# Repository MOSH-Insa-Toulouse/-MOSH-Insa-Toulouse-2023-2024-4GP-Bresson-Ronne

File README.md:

# -MOSH-Insa-Toulouse-2023-2024-4GP-Bresson-Ronne

Projet 4GP du capteur au banc de test en open source hardware
---
## Sommaire
  - [1) Contexte](#1-contexte)
  - [2) L'électronique Analogique](#2-L'électroniqueAnalogique)
  - [3) Kicad](#3-kicad)
  - [4) Le code Arduino](#4-lecodeArduino)
  - [5) L'application Bluetooth ](#5-l'appli)
  - [6) La DataSheet ](#6-data)
---

## 1) Contexte
Dans le cadre de l'UE "Du capteur au banc de test en Open Source Hardware", nous avons été amenés à réaliser un capteur de déformation low-tech à base de graphite. Le fonctionnement de ce capteur repose sur la variation de résistance engendrée par la déformation du matériau. La physique sous-jacente à cette variation de résistance provient du déplacement des électrons par effet tunnel entre les nanoparticules de graphite. Lorsqu'une contrainte mécanique est appliquée, la distance entre les nanoparticules varie, ce qui modifie la conductivité du graphite. Cette modification entraîne ainsi une variation de la résistance du capteur.<br>
Ce capteur est ensuite connnecté à un arduino. Divers élements sont ajoutés à l'Arduino, un capeteur flex sensor industriel que l'on comparera à notre capteur LowTech maison, un écran Oled pour pouvoir afficher nos résultats et un encodeur rotatoire qui permet de se déplacer sur les menus de l'écran Oled. Un module bluetooth est aussi implémenté en vue de créer une application android pour visualiser nos données. 

<p align="center">
  
  <br>
  <i>Photo de l'installation</i>
</p>

## 2) L'électronique Analogique
Une partie importante de la chaîne d’acquisition pour notre capteur réside dans le
conditionnement du signal délivré par le capteur, c’est-à-dire l’amplifier et le filtrer
pour pouvoir l’exploiter. Afin d’utiliser les capacités de la carte Arduino au maximum
(en pleine échelle), le gain du circuit d’amplification est variable grâce à la résistance
R2, ajustée par un potentiomètre digital.<br>
Le filtrage est effectué à plusieurs niveaux (avant et après amplification). Il y a donc 3
étages, chacun avec une fréquence de coupure différente, pour limiter le bruit au
maximum. Le circuit est modélisé dans LTSpice, afin d’effectuer des simulations. Il
faut noter qu’ici on peut se permettre d’avoir un filtrage fort à des fréquences très
faibles car à priori notre capteur ne sera pas utilisé à plus qu’environ 1Hz. Les
résultats obtenus par les simulations et un exemple de simulation (Diagramme de
Bode pour un étage sont présentés sur les figures suivantes. Le circuit LTSpice est à
trouver dans le dossier « électronique analogique ».

<p align="center">
  
  <br>
  <i>Caractéristiques de l'AOP</i>
</p>

<p align="center">
  
  <br>
  <i>Diagramme de Bode du premier étage de l'AOP</i>
</p>

## 3) Kicad
Afin de réaliser en pratique le circuit modélisé dans LTSpice, ainsi qu’ajouter tous les
composants liés à notre chaîne d’acquisition et aux capteurs, le logiciel KiCad est
utilisé. Il permet à partir d’un schéma électrique, créé dans un premier temps, et de
l’ajout des empreintes et modèles 3D des différents composants, de modéliser le
PCB et ses pistes électroniques, et d’en obtenir un modèle 3D. Ces documents sont
disponibles dans le dossier « KiCad ». Avec l’aide de Catherine Crouzet, nous avons
ensuite pu fabriquer notre PCB y souder les composants pour tester toute notre
chaîne d’acquisition, qui s’est avérée fonctionnelle directement.

<p align="center">
  
  <br>
  <i>Schéma du PCB réalisé sur KiCad</i>
</p>

## 4) Le code Arduino

Un code Arduino est implémenté sur un ArduinoUno. Le code permet d'afficher les valeurs de résistance sur l'écran oled et de choisir quel capteur est affiché via un encodeur rotatoire. Les valeurs de résitances sont aussi disponibles sur le serialmonitor ainsi que sur le téléphone. 

## 5) Lapplication 
L’application Android, créée avec le MIT App Inventor, permet de dialoguer via Bluetooth
(bouton de connexion à activer) avec la carte Arduino pour obtenir les valeurs de
résistance/angle fournies par le capteur. L’utilisateur peut choisir un nombre de mesures à
effectuer, le moment pour les lancer, puis ces mesures sont affichées en live sur un
indicateur numérique, un graphique, et exportées dans un tableur afin de les exploiter au
mieux. Un fichier APK est téléchargeable dans le dossier « Application Android »

<p align="center">
  
  <br>
  <i>Schéma de l'application Android</i>
</p>

## 6) La DataSheet 
La data sheet du capteur est disponible  [ici](https://github.com/MOSH-Insa-Toulouse/2023-2024-4GP-Bresson-Ronne/blob/main/DataSheet/datasheetCapteurBressonRonne.pdf).

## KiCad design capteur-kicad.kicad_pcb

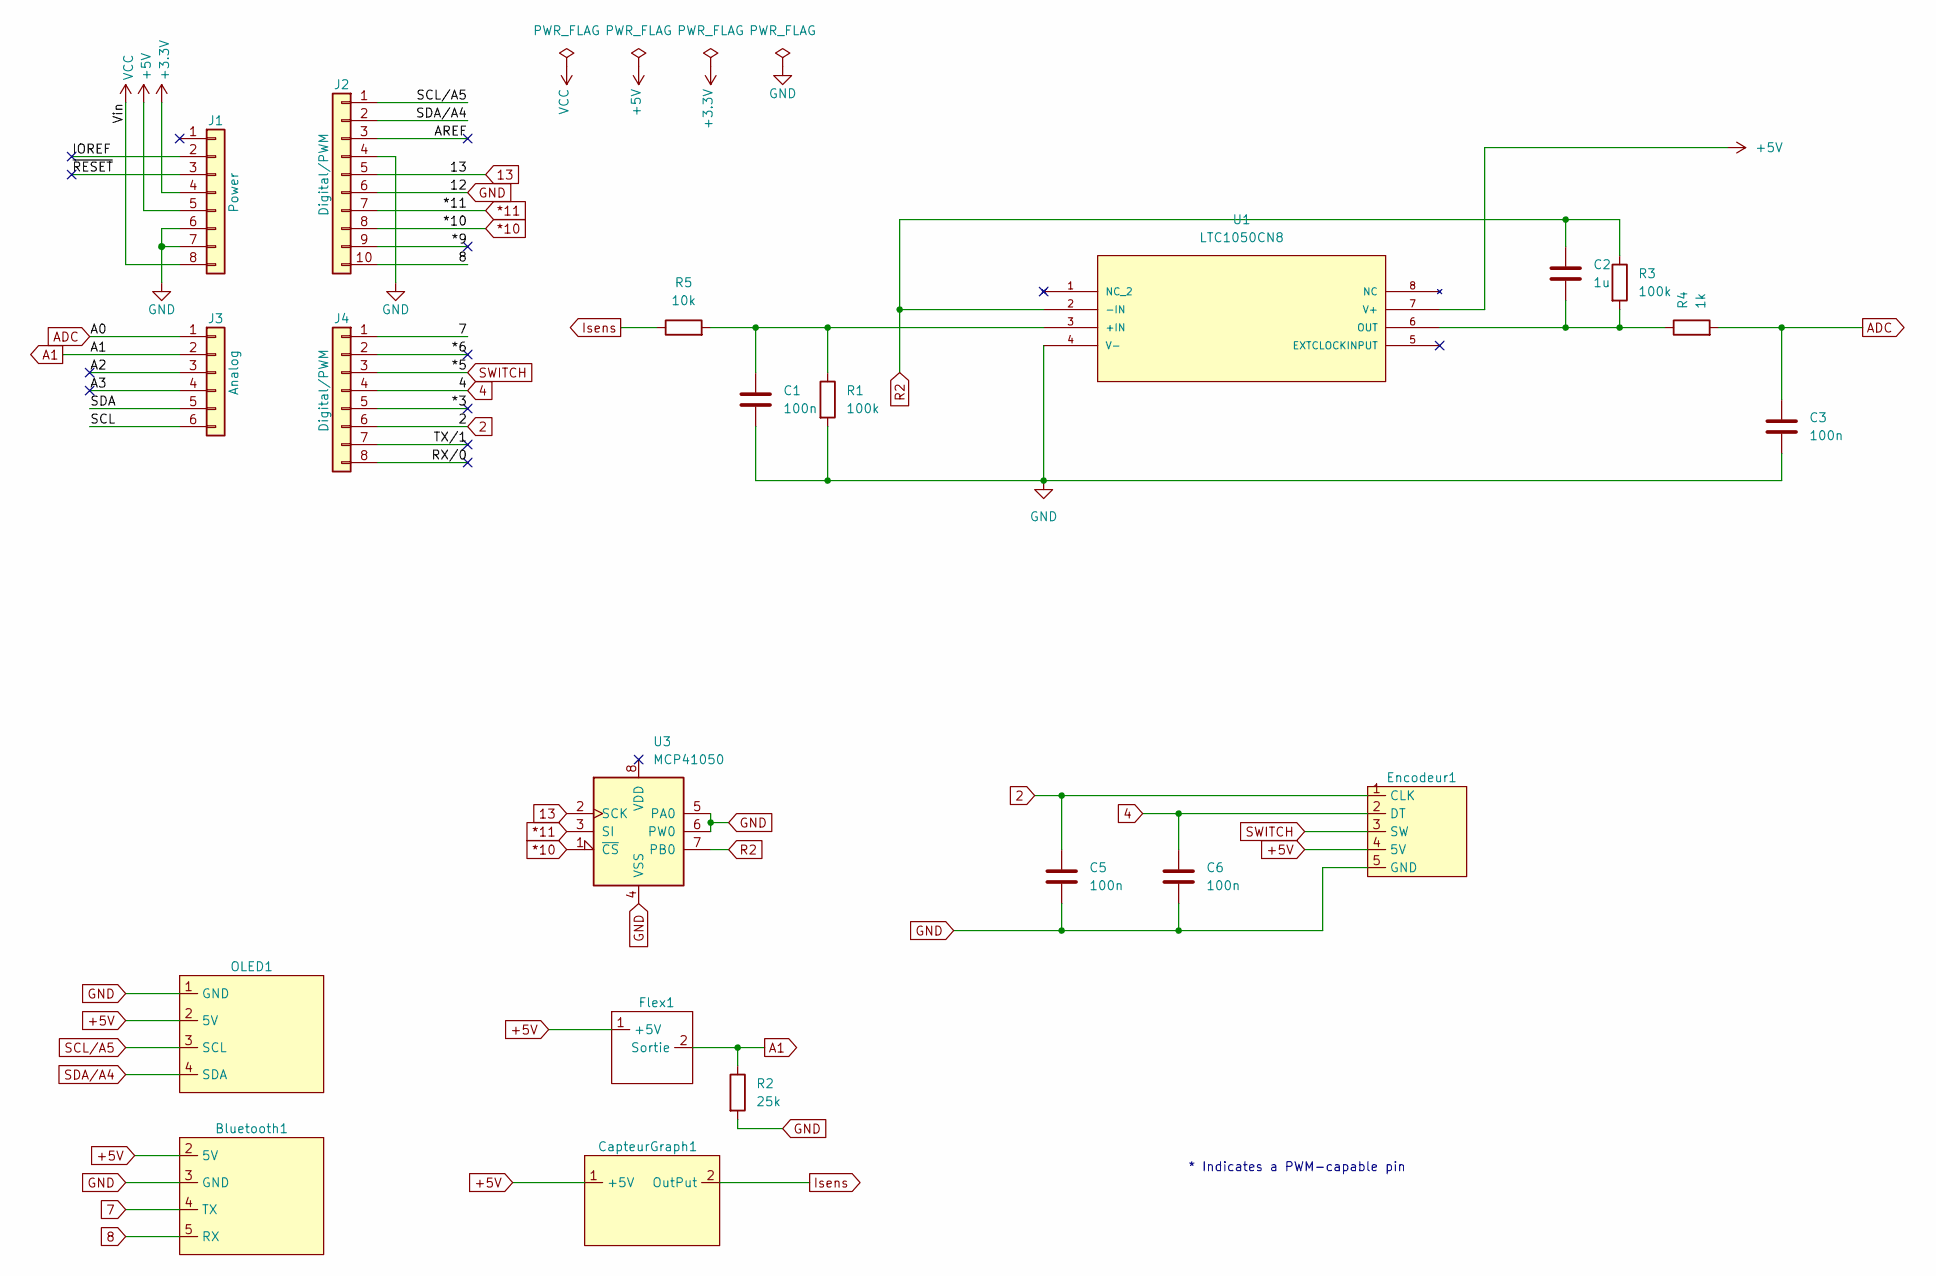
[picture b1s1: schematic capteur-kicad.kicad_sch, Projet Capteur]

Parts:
Bluetooth1: PinSocket_1x06_P2.54mm_Vertical
C1, C3, C5, C6: 100n; C_Axial_L3.8mm_D2.6mm_P7.50mm_Horizontal
C2: 1u; C_Rect_L9.0mm_W2.5mm_P7.50mm_MKT
CapteurGraph1: PinSocket_1x02_P2.54mm_Vertical
Encodeur1: PinSocket_1x05_P2.54mm_Vertical
Flex1: PinSocket_1x02_P2.54mm_Vertical
J1: Power; PinSocket_1x08_P2.54mm_Vertical
J2: Digital/PWM; PinSocket_1x10_P2.54mm_Vertical
J3: Analog; PinSocket_1x06_P2.54mm_Vertical
J4: Digital/PWM; PinSocket_1x08_P2.54mm_Vertical
OLED1: PinSocket_1x04_P2.54mm_Vertical
R1: 100k; R_Axial_DIN0207_L6.3mm_D2.5mm_P2.54mm_Vertical
R2: 25k; R_Axial_DIN0204_L3.6mm_D1.6mm_P7.62mm_Horizontal
R3: 100k; R_Axial_DIN0204_L3.6mm_D1.6mm_P7.62mm_Horizontal
R4: 1k; R_Axial_DIN0204_L3.6mm_D1.6mm_P7.62mm_Horizontal
R5: 10k; R_Axial_DIN0204_L3.6mm_D1.6mm_P7.62mm_Horizontal
U1: LTC1050CN8; DIP-8_W7.62mm; MANUFACTURER_PART_NUMBER ltc1050cn8
U3: MCP41050; DIP-8_W7.62mm

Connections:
2: C5.1, Encodeur1.1 (CLK), J4.6
4: C6.1, Encodeur1.2 (DT), J4.4
7: Bluetooth1.4 (TX), J4.1
8: Bluetooth1.5 (RX), J2.10
13: J2.5, U3.2 (SCK)
*10: J2.8, U3.1 (~CS)
*11: J2.7, U3.3 (SI)
+3V3: J1.4
+5V: Bluetooth1.2 (5V), CapteurGraph1.1 (+5V), Encodeur1.4 (5V), Flex1.1 (+5V), J1.5, OLED1.2 (5V), U1.7 (V+)
/*3: J4.5
/*6: J4.2
/*9: J2.9
/A2: J3.3
/A3: J3.4
/AREF: J2.3
/IOREF: J1.2
/RX/0: J4.8
/SCL: J3.6
/SDA: J3.5
/TX/1: J4.7
/~RESET: J1.3
A1: Flex1.2 (Sortie), J3.2, R2.1
ADC: C3.1, J3.1, R4.2
GND: Bluetooth1.3 (GND), C1.2, C3.2, C5.2, C6.2, Encodeur1.5 (GND), J1.6, J1.7, J2.4, J2.6, OLED1.1 (GND), R1.2, R2.2, U1.4 (V-), U3.4 (VSS), U3.5 (PA0), U3.6 (PW0)
Isens: CapteurGraph1.2 (OutPut), R5.1
unnamed: C1.1, R1.1, R5.2, U1.3 (+IN)
unnamed: C2.2, R3.2, R4.1, U1.6 (OUT)
R2: C2.1, R3.1, U1.2 (-IN), U3.7 (PB0)
SCL/A5: J2.1, OLED1.3 (SCL)
SDA/A4: J2.2, OLED1.4 (SDA)
SWITCH: Encodeur1.3 (SW), J4.3
VCC: J1.8

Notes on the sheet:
* Indicates a PWM-capable pin

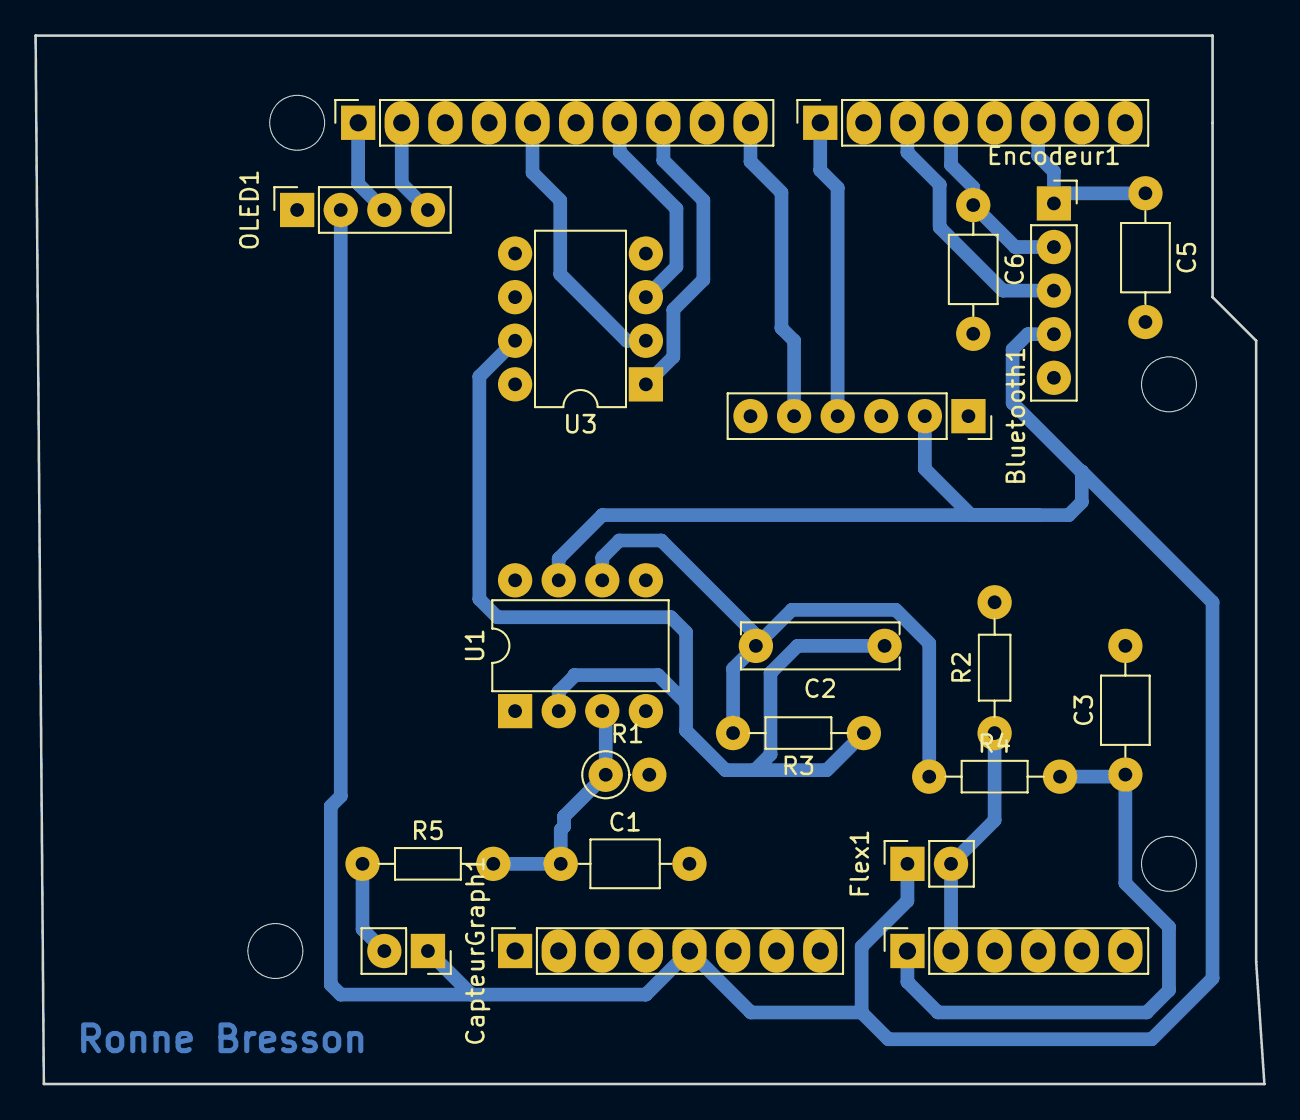
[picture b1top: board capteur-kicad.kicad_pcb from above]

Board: 2 copper layers, 71.6 x 61.1 mm, 25 parts (0 on the bottom side), 18 nets.

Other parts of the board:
MH1, MH2, MH3, MH4: MountingHole_3.2mm

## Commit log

2024-05-30 Create Images
2024-05-30 Create Code Arduino
2024-05-30 Create KiCad
2024-05-30 Create Appli Bluetooth
2024-06-07 KiCad
2024-06-07 LTspice
2024-06-07 Arduino

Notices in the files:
parts and their libraries:
COPYRIGHT: Copyright C 2016 Accelerated Designs. All rights reserved
